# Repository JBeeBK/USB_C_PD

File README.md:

# USB-C PD Power Meter and Debug Tool

This project is a compact, professional-grade USB-C Power Delivery (PD) debug tool and power meter. **Not finished yet tho.**
It’s designed to showcase modern hardware stuffs (USB-C, PD negotiation, embedded control, current/voltage sensing).
---

## Features

- **USB-C PD Sink (STUSB4500)**: negotiates 5 V / 9 V / 12 V / 15 V / 20 V profiles.  
- **Current and Voltage Monitoring**: INA219 + voltage divider for real-time display.  
- **I²C OLED Menu System**: user-selectable voltage and output control with buttons.  
- **Temperature Monitoring**: TMP112 tracks board temperature for safety.  
- **Visual Indicators**: LEDs show active voltage selection (5 V–20 V).  
- **Output Flexibility**: USB-C and screw terminal outputs (user selects output).  
- **MCU Control**: STM32G030 (TSOP-20) manages I²C devices, UI, and safety cutoffs.  
- **Designed in KiCad 9**: manufacturable layout, not just breadboard-friendly.

---

## Current Status

- **Schematic completed** (`00_Hardware`).  
- **First-round PCB layout completed** (see image below).  
- full check and BOM completion are next

---

## Board Preview

### Top View (First Layout)

---

## Repository Structure
- 00_Hardware/ # KiCad schematic, PCB, footprints, symbols.
- 01_Docs/ # Design notes, app notes, calculations.
- 02_Datasheets/ # Datasheets here.
- 03_Output_PCB/ # Gerbers.
- 04_Output_Assembly/ # Board renders and fabrication files.
- USB_PD_JB-backups/ # Auto-saved KiCad backups
- output generator python script
- README.md
- .gitignore

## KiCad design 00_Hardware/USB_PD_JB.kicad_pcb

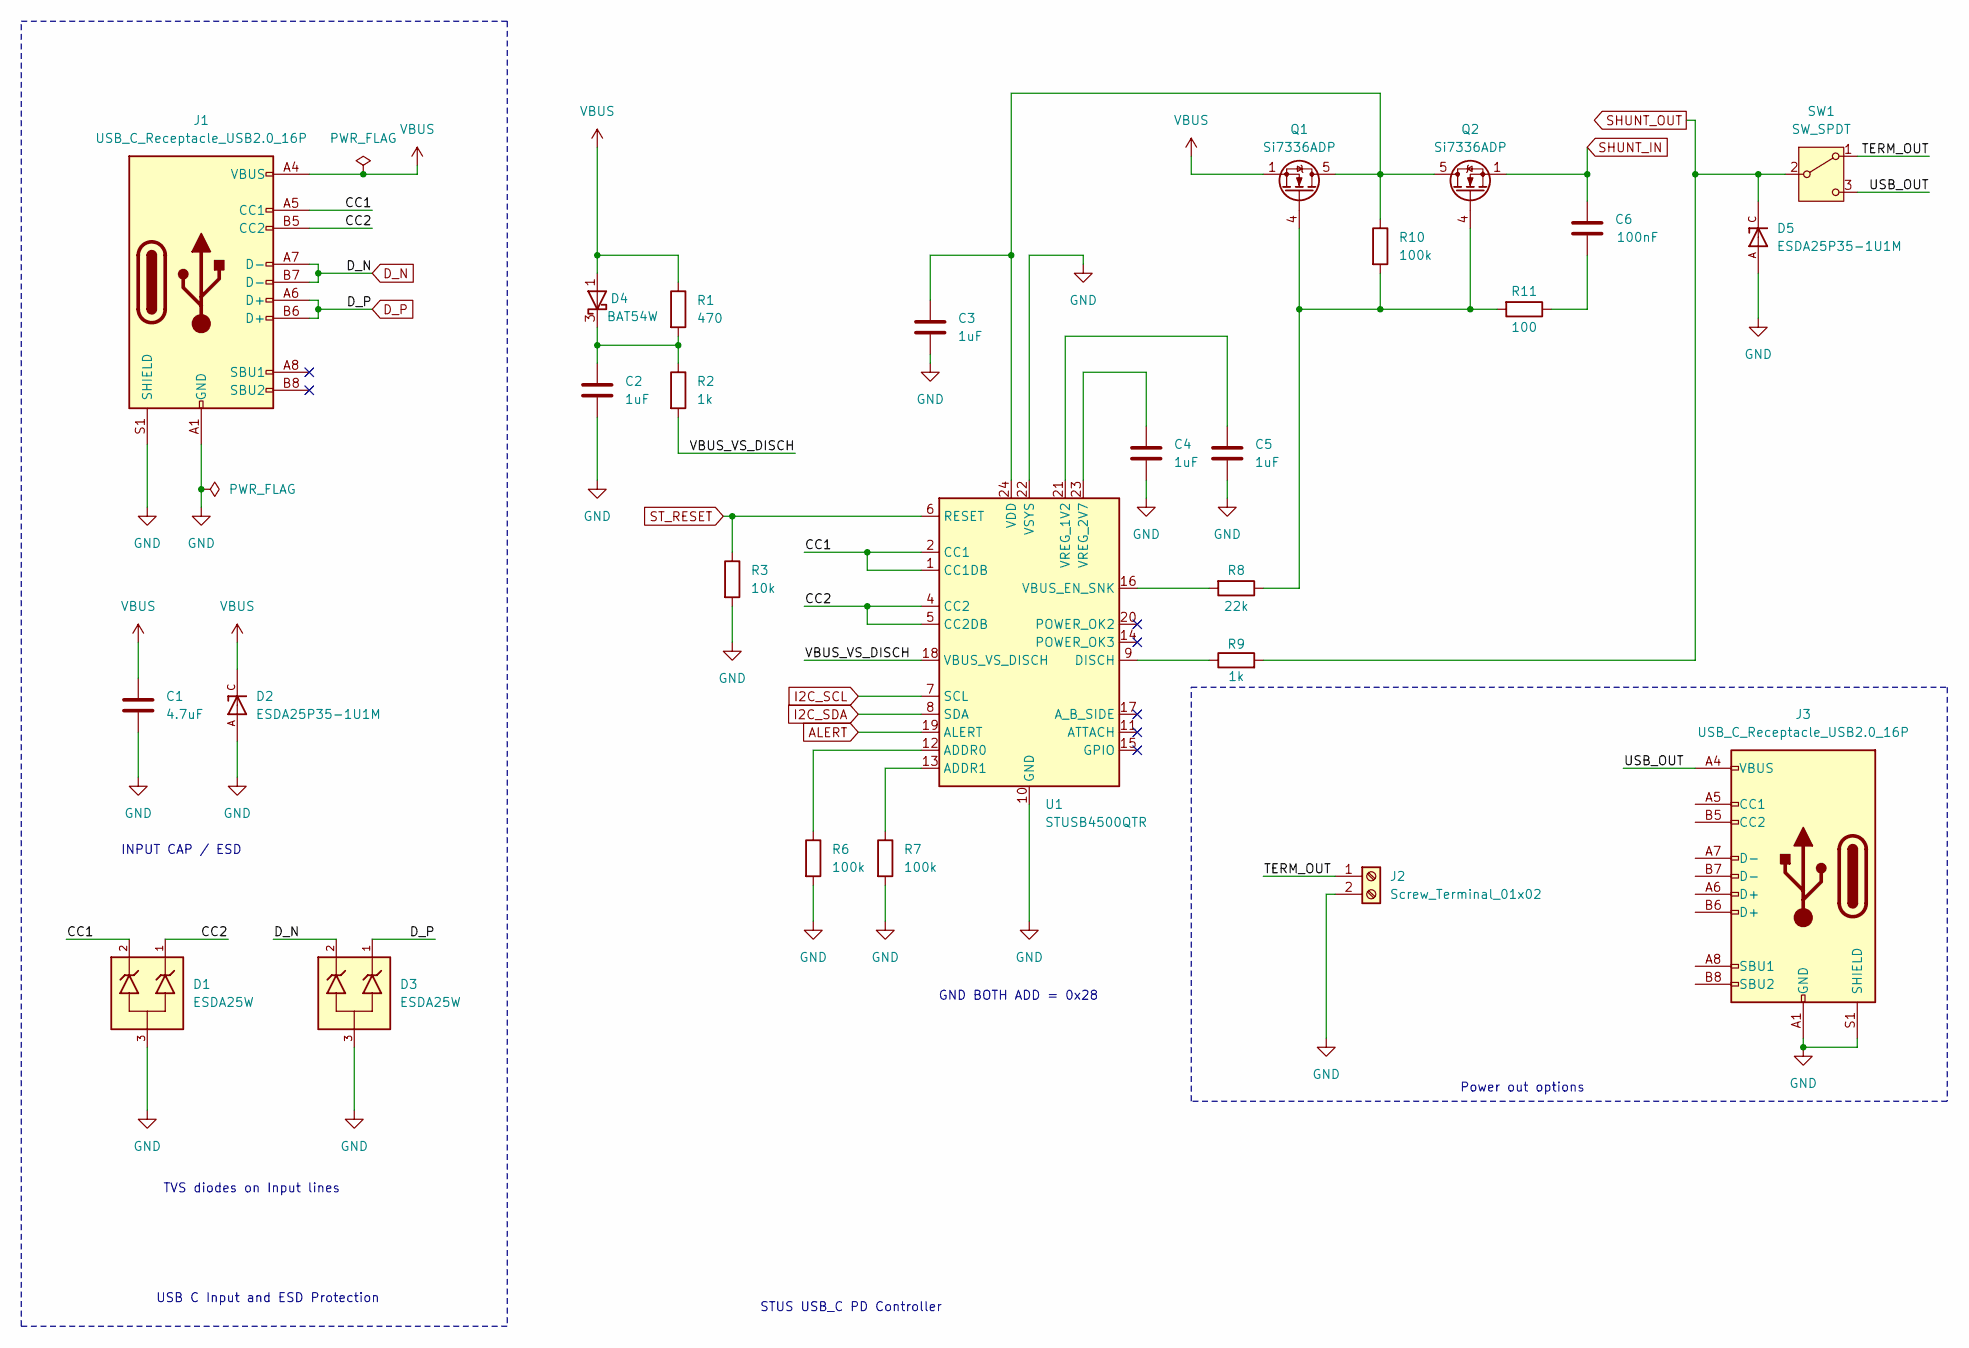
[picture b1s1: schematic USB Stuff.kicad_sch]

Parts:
C1: 4.7uF; C_0805_2012Metric
C2: 1uF; C_0805_2012Metric
C3, C4, C5: 1uF; C_0603_1608Metric
C6: 100nF; C_0603_1608Metric
D1, D3: ESDA25W; SOT65P210X110-3N; MPN1 ESDA25W
D2, D5: ESDA25P35-1U1M; TVS_ESDA25P35-1U1M; MPN1 ESDA25P35-1U1M
D4: BAT54W; SOT-323_SC-70
J1, J3: USB_C_Receptacle_USB2.0_16P; USB_C_Receptacle_GCT_USB4085
J2: Screw_Terminal_01x02; TerminalBlock_Phoenix_MKDS-1,5-2-5.08_1x02_P5.08mm_Horizont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; MPN1 MKDSN 1,5/2-5,08
Q1, Q2: Si7336ADP; LFPAK33
R1: 470; R_0805_2012Metric
R2, R9: 1k; R_0805_2012Metric
R3: 10k; R_0805_2012Metric
R6, R7, R10: 100k; R_0805_2012Metric
R8: 22k; R_0805_2012Metric
R11: 100; R_0805_2012Metric
SW1: SW_SPDT; 500SSP1S2M2QEA
U1: STUSB4500QTR; QFN-24-1EP_4x4mm_P0.5mm_EP2.7x2.7mm

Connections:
/USB Stuff/CC1: D1.2, J1.A5 (CC1), U1.1 (CC1DB), U1.2 (CC1)
/USB Stuff/CC2: D1.1, J1.B5 (CC2), U1.4 (CC2), U1.5 (CC2DB)
/USB Stuff/TERM_OUT: J2.1, SW1.1 (A)
/USB Stuff/USB_OUT: J3.A4 (VBUS), J3.A9 (VBUS), J3.B4 (VBUS), J3.B9 (VBUS), SW1.3 (C)
/USB Stuff/VBUS_VS_DISCH: R2.2, U1.18 (VBUS_VS_DISCH)
ALERT: U1.19 (ALERT)
D_N: D3.2, J1.A7 (D-), J1.B7 (D-); also elsewhere on the board
D_P: D3.1, J1.A6 (D+), J1.B6 (D+); also elsewhere on the board
GND: C1.2, C2.2, C3.2, C4.2, C5.2, D1.3, D2.A, D3.3, D5.A, J1.A1 (GND), J1.A12 (GND), J1.B1 (GND), J1.B12 (GND), J1.S1 (SHIELD), J2.2, J3.A1 (GND), J3.A12 (GND), J3.B1 (GND), J3.B12 (GND), J3.S1 (SHIELD), R3.2, R6.2, R7.2, U1.10 (GND), U1.22 (VSYS), U1.25 (GND); also elsewhere on the board
I2C_SCL: U1.7 (SCL); also elsewhere on the board
I2C_SDA: U1.8 (SDA); also elsewhere on the board
unnamed: C6.2, R11.1
unnamed: C2.1, D4.3 (K), R1.2, R2.1
unnamed: C3.1, Q1.5 (D), Q2.5 (D), R10.1, U1.24 (VDD)
unnamed: Q1.4 (G), Q2.4 (G), R8.1, R10.2, R11.2
unnamed: R6.1, U1.12 (ADDR0)
unnamed: R7.1, U1.13 (ADDR1)
unnamed: R9.1, U1.9 (DISCH)
unnamed: R8.2, U1.16 (VBUS_EN_SNK)
unnamed: C5.1, U1.21 (VREG_1V2)
unnamed: C4.1, U1.23 (VREG_2V7)
SHUNT_IN: C6.1, Q2.1 (S), Q2.2 (S), Q2.3 (S); also elsewhere on the board
SHUNT_OUT: D5.C, R9.2, SW1.2 (B); also elsewhere on the board
ST_RESET: R3.1, U1.6 (RESET); also elsewhere on the board
VBUS: C1.1, D2.C, D4.1 (A), J1.A4 (VBUS), J1.A9 (VBUS), J1.B4 (VBUS), J1.B9 (VBUS), Q1.1 (S), Q1.2 (S), Q1.3 (S), R1.1; also elsewhere on the board

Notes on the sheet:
Power out options
USB C Input and ESD Protection
GND BOTH ADD = 0x28
TVS diodes on Input lines
INPUT CAP / ESD
STUS USB_C PD Controller

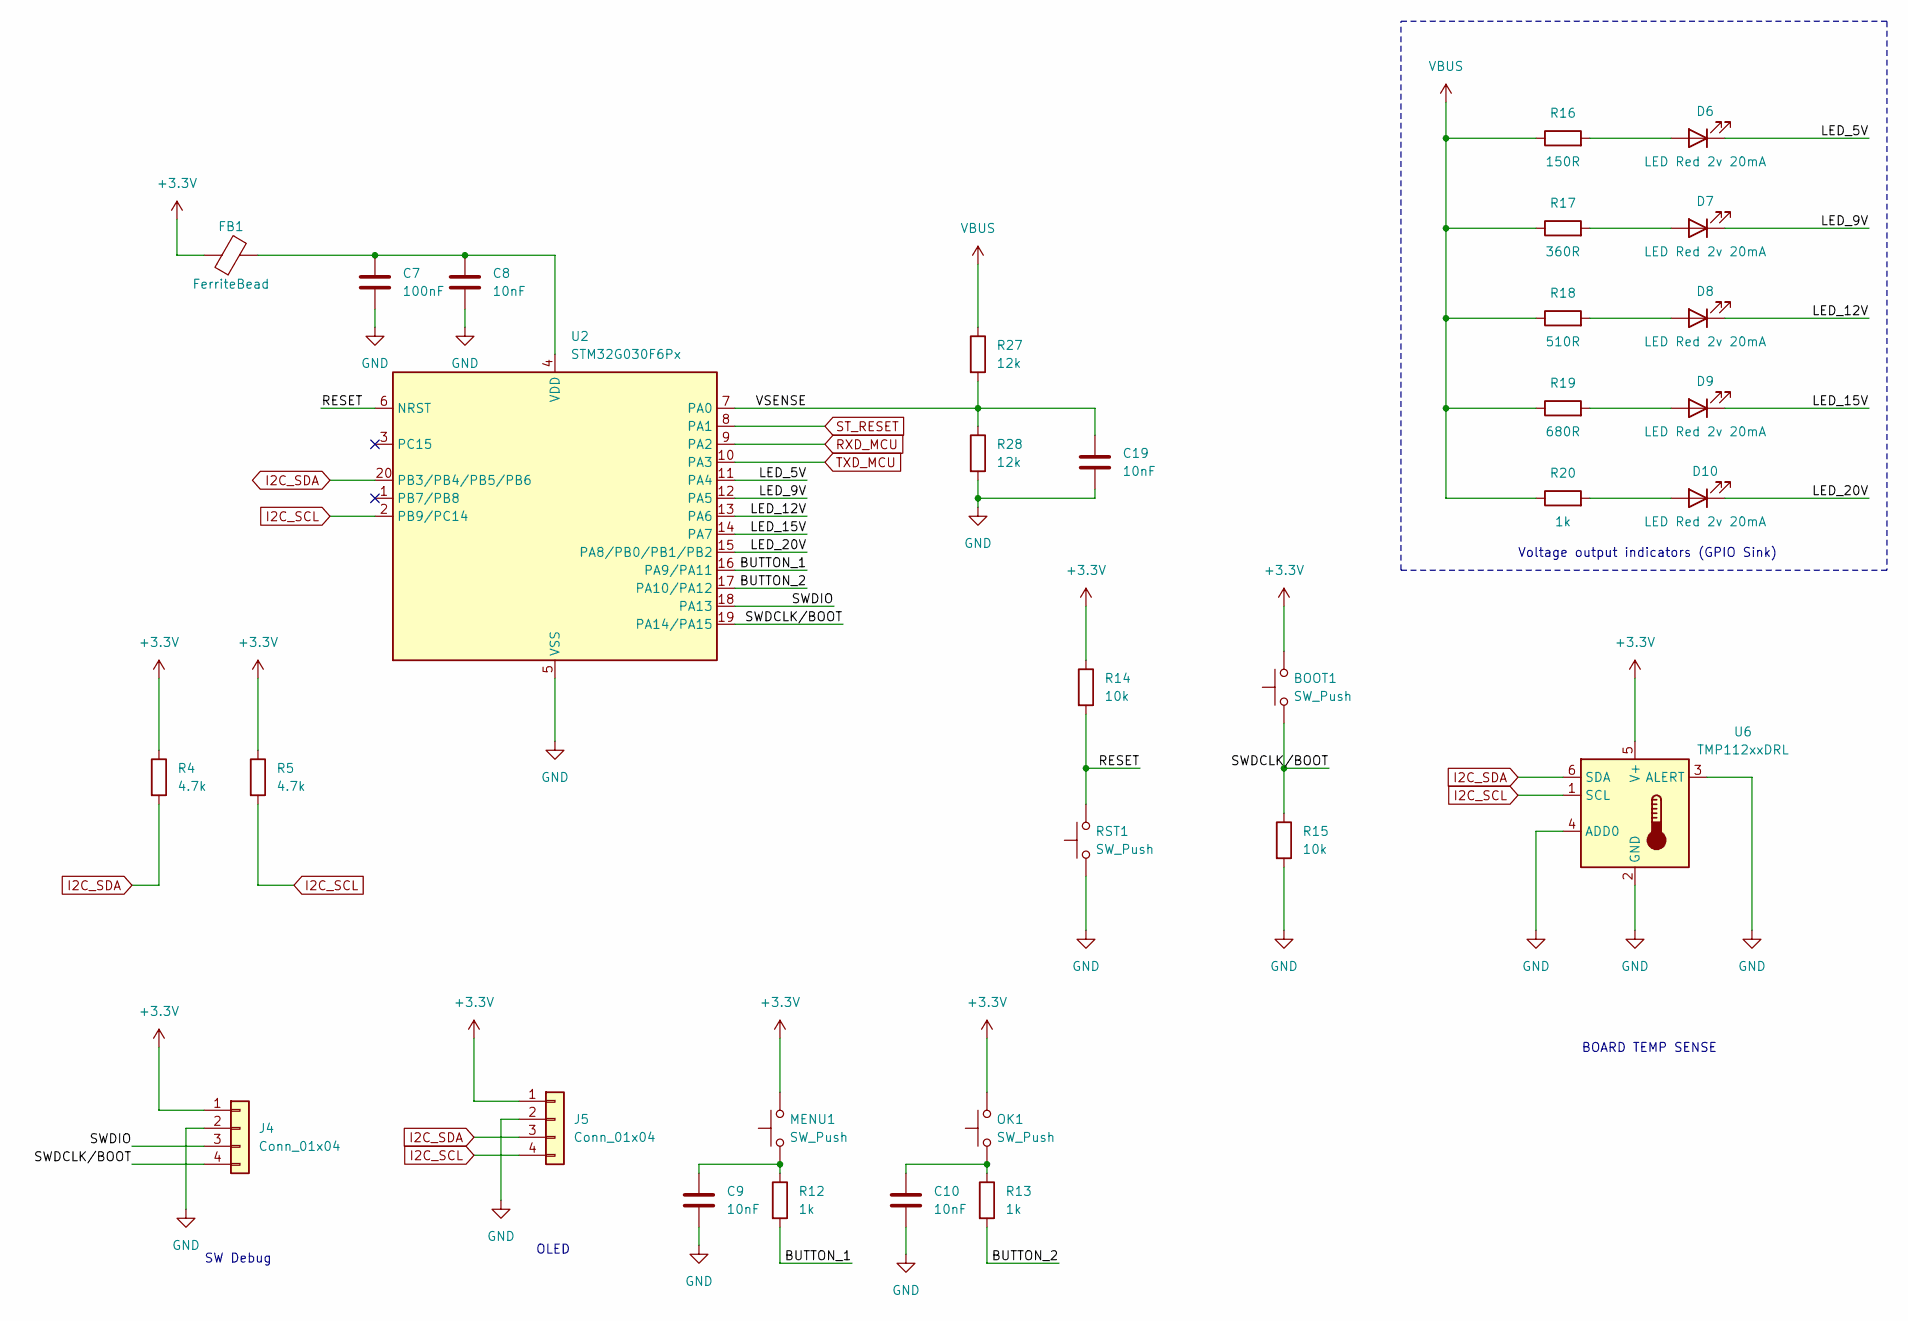
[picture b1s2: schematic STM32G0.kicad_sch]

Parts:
BOOT1: SW_Push; KMR211NGLFS
C7: 100nF; C_0603_1608Metric
C8, C9, C10, C19: 10nF; C_0603_1608Metric
D6, D7, D8, D9, D10: LED Red 2v 20mA; LED_0805_2012Metric; MPN1 APT2012SYCK
FB1: FerriteBead; L_0805_2012Metric
J4, J5: Conn_01x04; PinHeader_1x04_P2.54mm_Vertical
MENU1: SW_Push; SW_PUSH_6mm_H5mm
OK1: SW_Push; SW_PUSH_6mm_H5mm
R4, R5: 4.7k; R_0603_1608Metric
R12, R13: 1k; R_0603_1608Metric
R14, R15: 10k; R_0603_1608Metric
R16: 150R; R_0805_2012Metric
R17: 360R; R_0805_2012Metric
R18: 510R; R_0805_2012Metric
R19: 680R; R_0805_2012Metric
R20: 1k; R_0805_2012Metric
R27, R28: 12k; R_0603_1608Metric
RST1: SW_Push; KMR211NGLFS
U2: STM32G030F6Px; TSSOP-20_4.4x6.5mm_P0.65mm
U6: TMP112xxDRL; SOT-563

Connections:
+3.3V: BOOT1.2, FB1.1, J4.1, J5.1, MENU1.2, OK1.2, R4.1, R5.1, R14.1, U6.5 (V+); also elsewhere on the board
/STM32G0/BUTTON_1: R12.2, U2.16 (PA9/PA11)
/STM32G0/BUTTON_2: R13.2, U2.17 (PA10/PA12)
/STM32G0/LED_5V: D6.1 (K), U2.11 (PA4)
/STM32G0/LED_9V: D7.1 (K), U2.12 (PA5)
/STM32G0/LED_12V: D8.1 (K), U2.13 (PA6)
/STM32G0/LED_15V: D9.1 (K), U2.14 (PA7)
/STM32G0/LED_20V: D10.1 (K), U2.15 (PA8/PB0/PB1/PB2)
/STM32G0/RESET: R14.2, RST1.2, U2.6 (NRST)
/STM32G0/SWDCLK/BOOT: BOOT1.1, J4.4, R15.1, U2.19 (PA14/PA15)
/STM32G0/SWDIO: J4.3, U2.18 (PA13)
/STM32G0/VSENSE: C19.1, R27.2, R28.1, U2.7 (PA0)
GND: C7.2, C8.2, C9.2, C10.2, C19.2, J4.2, J5.2, R15.2, R28.2, RST1.1, U2.5 (VSS), U6.2 (GND), U6.3 (ALERT), U6.4 (ADD0); also elsewhere on the board
I2C_SCL: J5.4, R5.2, U2.2 (PB9/PC14), U6.1 (SCL); also elsewhere on the board
I2C_SDA: J5.3, R4.2, U2.20 (PB3/PB4/PB5/PB6), U6.6 (SDA); also elsewhere on the board
unnamed: C9.1, MENU1.1, R12.1
unnamed: C10.1, OK1.1, R13.1
unnamed: D6.2 (A), R16.2
unnamed: D7.2 (A), R17.2
unnamed: D8.2 (A), R18.2
unnamed: D9.2 (A), R19.2
unnamed: D10.2 (A), R20.2
unnamed: C7.1, C8.1, FB1.2, U2.4 (VDD)
RXD_MCU: U2.9 (PA2); also elsewhere on the board
ST_RESET: U2.8 (PA1); also elsewhere on the board
TXD_MCU: U2.10 (PA3); also elsewhere on the board
VBUS: R16.1, R17.1, R18.1, R19.1, R20.1, R27.1; also elsewhere on the board

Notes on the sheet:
OLED
BOARD TEMP SENSE
SW Debug
Voltage output indicators (GPIO Sink)

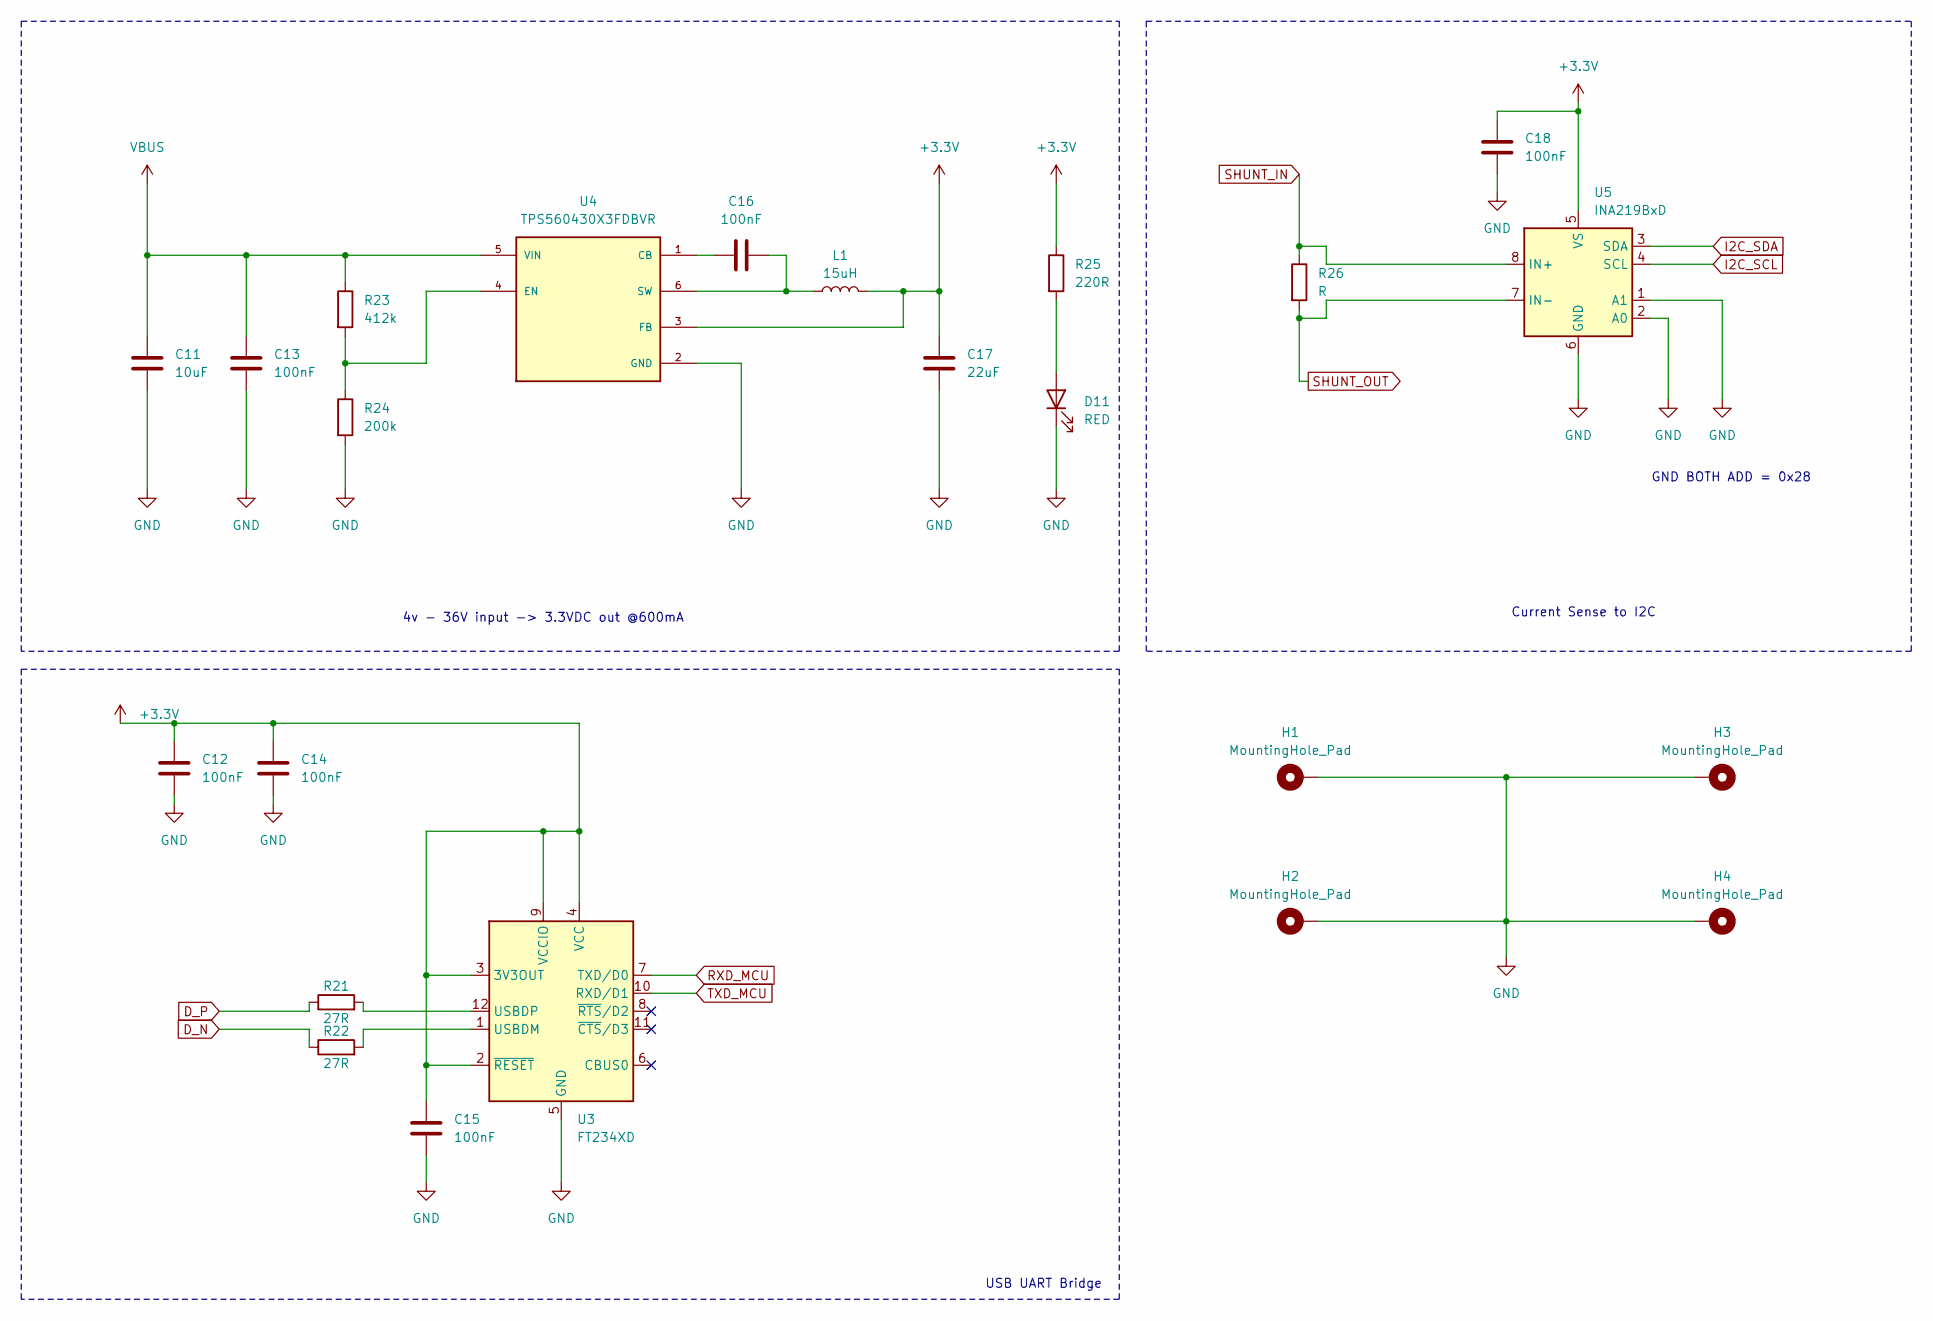
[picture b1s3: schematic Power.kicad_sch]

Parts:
C11: 10uF; C_1210_3225Metric; MPN1 GRM32ER71J106KA12L
C12, C13, C14, C15, C16, C18: 100nF; C_0603_1608Metric
C17: 22uF; C_0805_2012Metric
D11: RED; LED_0805_2012Metric; MPN1 APT2012SURCK
H1, H2, H3, H4: MountingHole_Pad; MountingHole_3.2mm_M3_DIN965_Pad_TopBottom
L1: 15uH; L_Coilcraft_LPS4018; MPN1 LPS4018-153MR
R21, R22: 27R; R_0603_1608Metric
R23: 412k; R_0603_1608Metric
R24: 200k; R_0603_1608Metric
R25: 220R; R_0805_2012Metric
R26: R; R_2816_7142Metric; MPN1 WSL2512R0100FEA
U3: FT234XD; DFN-12-1EP_3x3mm_P0.45mm_EP1.65x2.38mm
U4: TPS560430X3FDBVR; SOT-23-6; PARTREV B
U5: INA219BxD; SOIC-8_3.9x4.9mm_P1.27mm

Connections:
+3.3V: C12.1, C14.1, C15.1, C17.1, C18.1, L1.2, R25.1, U3.2 (~RESET), U3.3 (3V3OUT), U3.4 (VCC), U3.9 (VCCIO), U4.3 (FB), U5.5 (VS); also elsewhere on the board
D_N: R22.1; also elsewhere on the board
D_P: R21.1; also elsewhere on the board
GND: C11.2, C12.2, C13.2, C14.2, C15.2, C17.2, C18.2, D11.1 (K), H1.1, H2.1, H3.1, H4.1, R24.2, U3.5 (GND), U3.13 (GND), U4.2 (GND), U5.1 (A1), U5.2 (A0), U5.6 (GND); also elsewhere on the board
I2C_SCL: U5.4 (SCL); also elsewhere on the board
I2C_SDA: U5.3 (SDA); also elsewhere on the board
unnamed: D11.2 (A), R25.2
unnamed: R22.2, U3.1 (USBDM)
unnamed: R21.2, U3.12 (USBDP)
unnamed: C16.1, U4.1 (CB)
unnamed: R23.2, R24.1, U4.4 (EN)
unnamed: C16.2, L1.1, U4.6 (SW)
RXD_MCU: U3.7 (TXD/D0); also elsewhere on the board
SHUNT_IN: R26.1, U5.8 (IN+); also elsewhere on the board
SHUNT_OUT: R26.2, U5.7 (IN-); also elsewhere on the board
TXD_MCU: U3.10 (RXD/D1); also elsewhere on the board
VBUS: C11.1, C13.1, R23.1, U4.5 (VIN); also elsewhere on the board

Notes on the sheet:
Current Sense to I2C
4v - 36V input -> 3.3VDC out @600mA
GND BOTH ADD = 0x28
USB UART Bridge

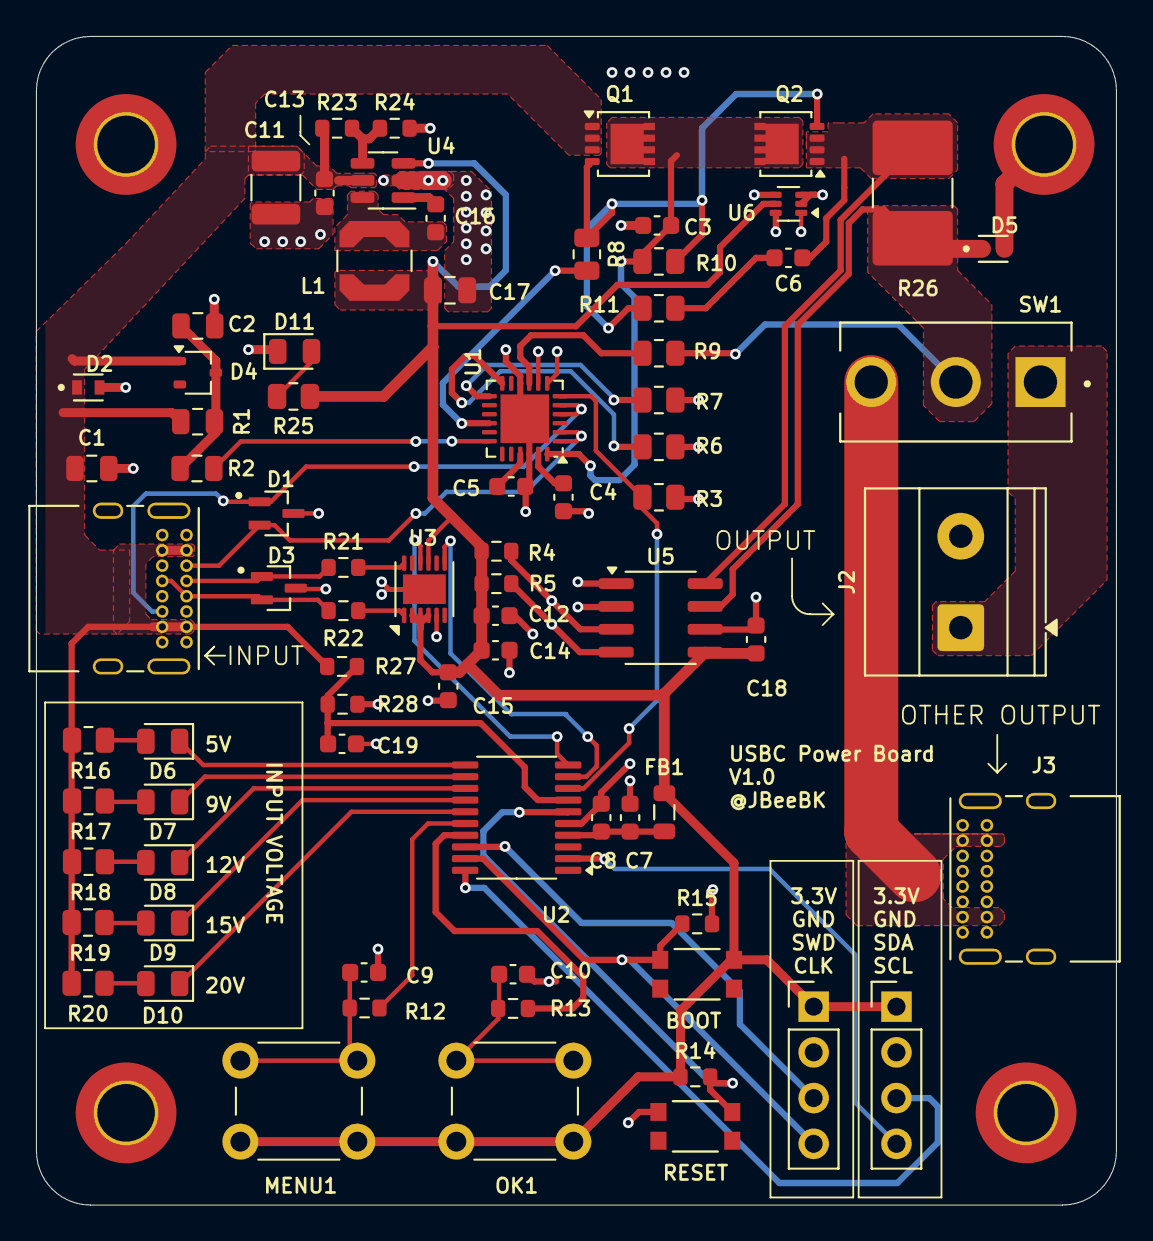
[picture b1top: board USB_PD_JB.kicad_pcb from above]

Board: 4 copper layers, 60.0 x 64.9 mm, 82 parts (0 on the bottom side), 52 nets.

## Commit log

2025-07-25 initial commit of schematic, transferring to another PC to continue
2025-07-28 First Routing w/ output files auto-generated
2025-07-29 updated silkscreen
2025-07-29 silkscreen update
2025-07-29 silkscreen
